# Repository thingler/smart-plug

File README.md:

# Thingler Smart Plug

Thingler Smart Plug is a 3D printed smart plug based on the popular ESP32 micro controller. This device is using the [Thingler ESP32-PICO Module](https://github.com/thingler/esp32-pico-module).

Software has been written to either connect to the [AWS IOT service](https://github.com/thingler/smart-plug-esp32) or it can use the [Matter connectrivity standard](https://github.com/thingler/smart-plug-matter).

## Getting started

### Requirements

* [KiCad](https://www.kicad.org/download/) for the schematics
* [Thingler ESP32-PICO Module](https://github.com/thingler/esp32-pico-module)
* Either [Thingler Smart Plug Matter](https://github.com/thingler/smart-plug-matter) or [Thinger Smart Plug ESP32 (AWS IoT)](https://github.com/thingler/smart-plug-esp32) for the ESP32 module
* [3D design](https://www.tinkercad.com/things/a5thrdSu9my)

### Build

#### Disclamer

Thingler Smart Plug is provided for informational and educational purposes only. The creator of the project and its contributors are not responsible for any damages, injuries, or losses that may result from building, modifying, or using the smart plug. Users assume all risks associated with building and using the smart plug, and should take all necessary precautions to ensure their safety. By using the smart plug or any information provided in this project, users agree to hold harmless the creator and contributors of the project from any and all claims, damages, or expenses that may arise.

> :warning: **Warning: The Smart Plug is designed to work with high voltage AC power from the electrical outlet. This voltage can be dangerous and even deadly if not handled properly. Only experienced individuals with proper training and knowledge should attempt to build this smart plug. If you are not experienced or confident in your ability to work with high voltage electricity, do not attempt to build or use this device. Improper use or handling of the smart plug can result in serious injury or death. Always take appropriate safety measures and precautions when working with high voltage electricity.**

> :warning: **Warning: The circuit does not provide galvanic isolation, which means that dangerous voltages from the AC power line can be present in the circuit. Do not attempt to connect any instruments or devices to the circuit while it is connected to the AC power line.**

#### Components

The PCB can be ordered from any fabrication houses by providing the [gerber files](Gerbers). Note that the copper weight should be 2 oz.

The following components has been used for Smart Plug:

| Ref | Qty | Manufacturer Part Number | Manufacturer | Description | Product Link |
| --- | --- | --- | --- | --- | --- |
| C1, C2, C3, C5, C6 | 5 | C1206C104M5RACTU | KEMET | Multilayer Ceramic Capacitors MLCC - SMD/SMT 50V 0.1uF X7R 1206 20% | [Mouser](https://www.mouser.com/ProductDetail/KEMET/C1206C104M5RACTU?qs=sGAEpiMZZMs0AnBnWHyRQAyQ3AEn5kTUXS61cVd4nXQ%3D) |
| C4 | 1 | TPSE477K010R0050 | KYOCERA AVX | Tantalum Capacitors - Solid SMD 10V 470uF 10% 2917 ESR= 50 mOhm | [Mouser](https://www.mouser.com/ProductDetail/KYOCERA-AVX/TPSE477K010R0050?qs=sGAEpiMZZMsh%252B1woXyUXjxWZTFtyFwDuJgYiJSpALQg%3D) |
| C7 | 1 | C3216X7S0J336M160AC | TDK | Multilayer Ceramic Capacitors MLCC - SMD/SMT 1206 6.3V 33uF X7S 20% T: 1.6mm | [Mouser](https://www.mouser.com/ProductDetail/TDK/C3216X7S0J336M160AC?qs=xLDY6iXSiQZFXqsBpUFNJw%3D%3D) |
| D1 | 1 | ABS10A-13 | Diodes Incorporated | Bridge Rectifier | [Mouser](https://www.mouser.com/ProductDetail/Diodes-Incorporated/ABS10A-13?qs=5aG0NVq1C4z7Y6XEf8aBrg%3D%3D) |
| F1 | 1 | 0679H1000-01 | Bel Fuse | Surface Mount Fuse 1A 350 VAC 72 VCD | [Mouser](https://www.mouser.com/ProductDetail/530-0679H1000-01) |
| J1-1 | 1 |  | ZHNL | Europe Standard Plug Insert, can only be acquired in big quantities (or as samples) | [Alibaba](https://www.alibaba.com/product-detail/Europe-Standard-Plug-Insert-two-2_1600487104594.html) |
| J1-2 | 1 |  | ZHNL | AMD European German socket, can only be acquired in big quantities (or as samples) | [Zhnlen](http://www.zhnlen.com/en/pd.jsp?recommendFromPid=0&id=221&fromMid=827&fromColId=116), [Alibaba](https://www.alibaba.com/product-detail/German-and-serbia-Terminal-Contact-Cage_1600497363416.html) |
| L1 | 1 | ME3220-123KLC | Coilcraft | Power Inductors - SMD 12uH Unshld 10% 840mA 470mOhms | [Mouser](https://www.mouser.com/ProductDetail/Coilcraft/ME3220-123KLC?qs=sGAEpiMZZMsg%252By3WlYCkU2kWFds1hA9DbYDsvlhd31E%3D) |
| Q1 | 1 | STGD5NB120SZT4 | STMicroelectronics | IGBT Transistors N-Ch 1200 Volt 5 Amp | [Mouser](https://www.mouser.com/ProductDetail/STMicroelectronics/STGD5NB120SZT4?qs=Tj7OqeScv5KzkQtpY0oojQ%3D%3D) |
| Q2 | 1 | BTA316B-600E,118 | WeEn Semiconductors | Triacs Thyristor TRIAC 600V 150A 3-Pin (2+Tab) | [Mouser](https://www.mouser.com/ProductDetail/WeEn-Semiconductors/BTA316B-600E118?qs=6YAT8rHPFU%252BjXw0I0rTt4g%3D%3D) |
| R1, R2 | 2 | CR1206AFX-2003EAS | Bourns | Thick Film Resistors - SMD ResA-AS 1206 200k 1% 250mW TC100 | [Mouser](https://www.mouser.com/ProductDetail/Bourns/CR1206AFX-2003EAS?qs=PzGy0jfpSMsbNqkCSMTFTg%3D%3D) |
| R3, R4 | 2 | KTR18EZPF5103 | ROHM Semiconductor | Thick Film Resistors - SMD 1206 510Kohm 1% High VoltageAEC-Q200 | [Mouser](https://www.mouser.com/ProductDetail/ROHM-Semiconductor/KTR18EZPF5103?qs=DyUWGjl%252BcVuYEq26lvIerQ%3D%3D) |
| R5 | 1 | CRCW1206210RFKEA | Vishay / Dale | Thick Film Resistors - SMD 1/4watt 210ohms 1% | [Mouser](https://www.mouser.com/ProductDetail/Vishay-Dale/CRCW1206210RFKEA?qs=LOE%2FbrHKynXo3sZGow1Zgw%3D%3D) |
| R6 | 1 | CRCW120680K6FKEA | Vishay / Dale | Thick Film Resistors - SMD 1/4watt 80.6Kohms 1% | [Mouser](https://www.mouser.com/ProductDetail/Vishay-Dale/CRCW120680K6FKEA?qs=sGAEpiMZZMtlubZbdhIBIIDv3ViF%2FKZ8GQ5VYt9J%2FQI%3D) |
| R7 | 1 | CR1206-FX-1242ELF | Bourns | Thick Film Resistors - SMD 12.4K 1% | [Mouser](https://www.mouser.com/ProductDetail/Bourns/CR1206-FX-1242ELF?qs=sGAEpiMZZMtlubZbdhIBICIt3wBox2Qh6Yrjo1PMsNo%3D) |
| R8 | 1 | ERJ-8ENF1800V | Panasonic | Thick Film Resistors 1206 180ohms 1% AEC-Q200 | [Mouser](https://www.mouser.com/ProductDetail/Panasonic/ERJ-8ENF1800V?qs=sGAEpiMZZMvdGkrng054t8AJgcdMkx7xp%2FUyp6%252BxK6s%3D) |
| U1 | 1 | THINGLER-ESP32-PICO | Thingler | ESP32 module | [GitHub](https://github.com/thingler/esp32-pico-module) |
| U2 | 1 | SR086SG-G | Microchip Technology / Atmel | Switching Voltage Regulators 3.3V Adjust Off-Line Switching Regulator | [Mouser](https://www.mouser.com/ProductDetail/Microchip-Technology-Atmel/SR086SG-G?qs=ph4zPCVRuvrOCUnBv7TdAA%3D%3D) |
| U3 | 1 | FODM3012R2V-NF098 | onsemi / Fairchild | Triac & SCR Output Optocouplers MFP, 250V Random Phase Triac Output | [Mouser](https://www.mouser.com/ProductDetail/onsemi-Fairchild/FODM3012R2V-NF098?qs=0lQeLiL1qyYTpyszibB5tA%3D%3D) |
| U4 | 1 | TPS560430X3FDBVR | Texas Instruments | Voltage Regulators - Switching Regulators SIMPLE SWITCHER 36-V, 600-mA Buck Regulator With High-Efficiency Sleep Mode 6-SOT-23 -40 to 125 | [Mouser](https://www.mouser.com/ProductDetail/Texas-Instruments/TPS560430X3FDBVR?qs=sGAEpiMZZMsMIqGZiACxIY79W%2FZ1FL4F65GEfpgrgpedxebpzRnU7w%3D%3D) |

#### Printing the 3D design

The smart plug case is designed to be printed without the need for any support material. We recommend using PETG filament as it is a strong and durable material suitable for this application. Please note that in addition to the printed case, you will also need the following components to assemble the smart plug:

* 2 x M2 nuts
* 2 x M2 * 8 screws

## License

Released under [GNU/GPL Version 3](LICENSE)

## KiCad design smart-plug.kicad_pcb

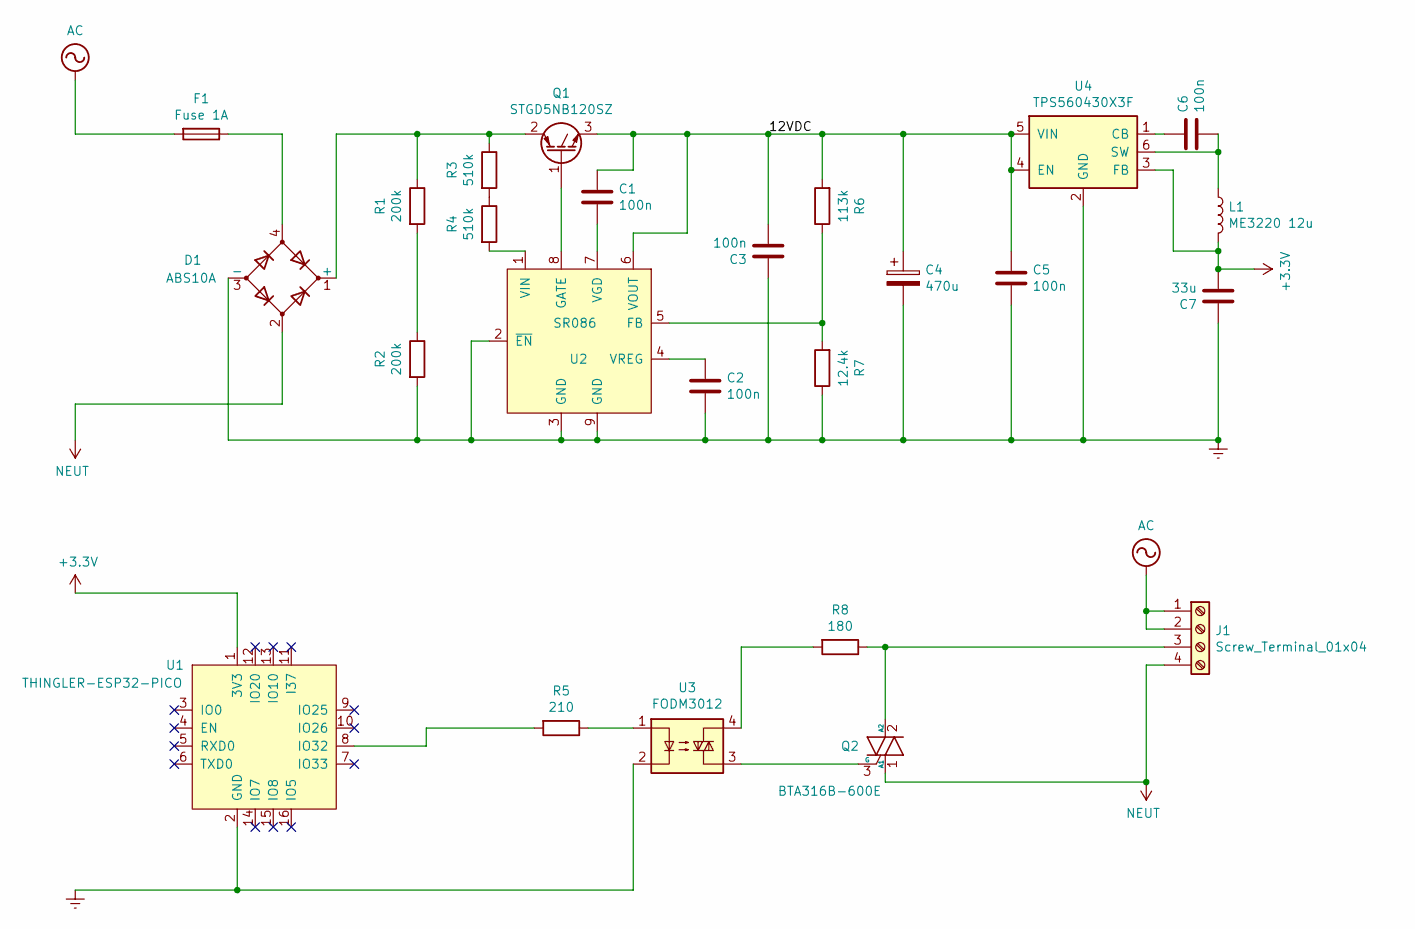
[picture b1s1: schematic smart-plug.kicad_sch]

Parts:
C1, C2, C3, C5, C6: 100n; C_1206_3216Metric_Pad1.42x1.75mm_HandSolder
C4: 470u; CP_EIA-7343-15_Kemet-W
C7: 33u; C_1206_3216Metric_Pad1.42x1.75mm_HandSolder
D1: ABS10A
F1: Fuse 1A; fuse-2410
J1: Screw_Terminal_01x04; 3d_power_connector
L1: ME3220 12u; ME3220
Q1: STGD5NB120SZ; TO-252-2
Q2: BTA316B-600E; to-263-2
R1, R2: 200k; R_1206_3216Metric_Pad1.42x1.75mm_HandSolder
R3, R4: 510k; R_1206_3216Metric_Pad1.42x1.75mm_HandSolder
R5: 210; R_1206_3216Metric_Pad1.42x1.75mm_HandSolder
R6: 113k; R_1206_3216Metric_Pad1.42x1.75mm_HandSolder
R7: 12.4k; R_1206_3216Metric_Pad1.42x1.75mm_HandSolder
R8: 180; R_1206_3216Metric_Pad1.42x1.75mm_HandSolder
U1: THINGLER-ESP32-PICO; Thingler-esp32-vertical
U2: SR086; SOIC-8-1EP_3.9x4.9mm_P1.27mm_EP2.29x3mm
U3: FODM3012
U4: TPS560430X3F; SOT-23-6

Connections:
+3V3: C7.2, L1.2, U1.1 (3V3), U4.3 (FB)
/12VDC: C1.1, C3.2, C4.1, C5.1, Q1.3 (E), R6.2, U2.6 (VOUT), U4.4 (EN), U4.5 (VIN)
AC: F1.2, J1.1, J1.2
Earth: C2.2, C3.1, C4.2, C5.2, C7.1, D1.3 (-), R2.2, R7.1, U1.2 (GND), U2.2 (~EN), U2.3 (GND), U2.9 (GND), U3.2, U4.2 (GND)
NEUT: D1.2, J1.4, Q2.1 (A1)
unnamed: C1.2, U2.7 (VGD)
unnamed: C2.1, U2.4 (VREG)
unnamed: C6.1, U4.1 (CB)
unnamed: C6.2, L1.1, U4.6 (SW)
unnamed: D1.1 (+), Q1.2 (C), R1.1, R3.1
unnamed: D1.4, F1.1
unnamed: J1.3, Q2.2 (A2), R8.1
unnamed: Q1.1 (G), U2.8 (GATE)
unnamed: Q2.3 (G), U3.3
unnamed: R1.2, R2.1
unnamed: R3.2, R4.1
unnamed: R4.2, U2.1 (VIN)
unnamed: R5.1, U3.1
unnamed: R5.2, U1.8 (IO32)
unnamed: R6.1, R7.2, U2.5 (FB)
unnamed: R8.2, U3.4

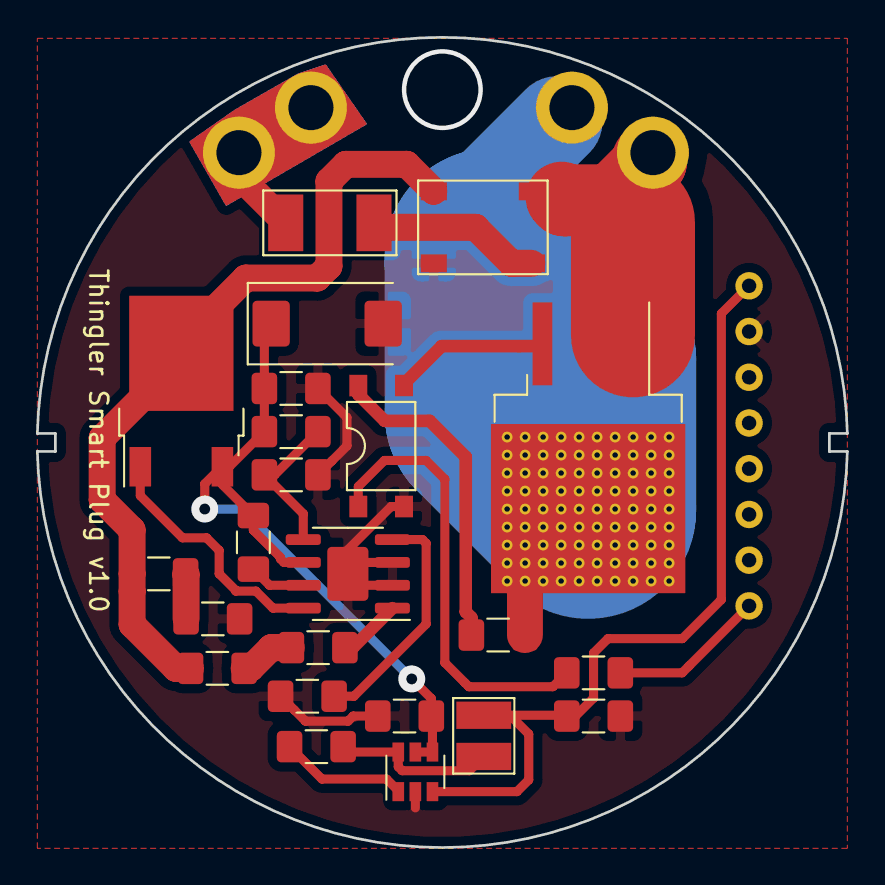
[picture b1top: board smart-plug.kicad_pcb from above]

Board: 2 copper layers, 45.0 x 45.0 mm, 25 parts (1 on the bottom side), 21 nets.

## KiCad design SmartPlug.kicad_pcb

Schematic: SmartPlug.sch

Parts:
C1: X2 150n; C_Axial_L12.0mm_D6.5mm_P15.00mm_Horizontal
C2: 47u; CP_Elec_10x10
C3, C4: 100n; C_1206_3216Metric_Pad1.42x1.75mm_HandSolder
C5: 33u; C_1206_3216Metric_Pad1.42x1.75mm_HandSolder
D1: D_Bridge; Diode_Bridge_Vishay_DFS
D2: 68V Zener; D_SMA_Handsoldering
D3: D_Schottky; D_SOD-123
J1: Conn_WallSocket; 230V_OUT
L1: 200u; L_Coilcraft_LPS4018
Q1: BTA 12/600SW; TO-220-3_Vertical
R1, R2: 383k; R_1206_3216Metric_Pad1.42x1.75mm_HandSolder
R3, R4: 100 1W; R_Axial_DIN0414_L11.9mm_D4.5mm_P15.24mm_Horizontal
R5: 100; R_1206_3216Metric_Pad1.42x1.75mm_HandSolder
R6: 180; R_1206_3216Metric_Pad1.42x1.75mm_HandSolder
R7: 1M; R_1206_3216Metric_Pad1.42x1.75mm_HandSolder
R8: 100k; R_1206_3216Metric_Pad1.42x1.75mm_HandSolder
U1: MAX5033AUSA; SOIC-8_3.9x4.9mm_P1.27mm
U2: ESP32-PICO-KIT
U3: MOC3021M; DIP-6_W8.89mm_SMDSocket_LongPads

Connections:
+3V3: C5.1, L1.2, U1.4, U2.20, U2.38
/+68V: C2.1, D2.1, R3.1, R7.2, U1.7
AC: C1.2, J1.1, R1.2
Earth: C2.2, C3.2, C5.2, D1.2, D2.2, D3.2, R8.1, U1.3, U1.6, U2.19, U2.39, U3.2
NEUT: Q1.1 (A1), R4.2
unnamed: C1.1, D1.3, R2.1
unnamed: C3.1, U1.2
unnamed: C4.1, U1.1
unnamed: C4.2, D3.1, L1.1, U1.8
unnamed: D1.1, R3.2
unnamed: D1.4, R4.1
unnamed: J1.2, Q1.2 (A2), R6.1
unnamed: Q1.3 (G), U3.4
unnamed: R1.1, R2.2
unnamed: R5.1, U3.1
unnamed: R5.2, U2.29
unnamed: R6.2, U3.6
unnamed: R7.1, R8.2, U1.5

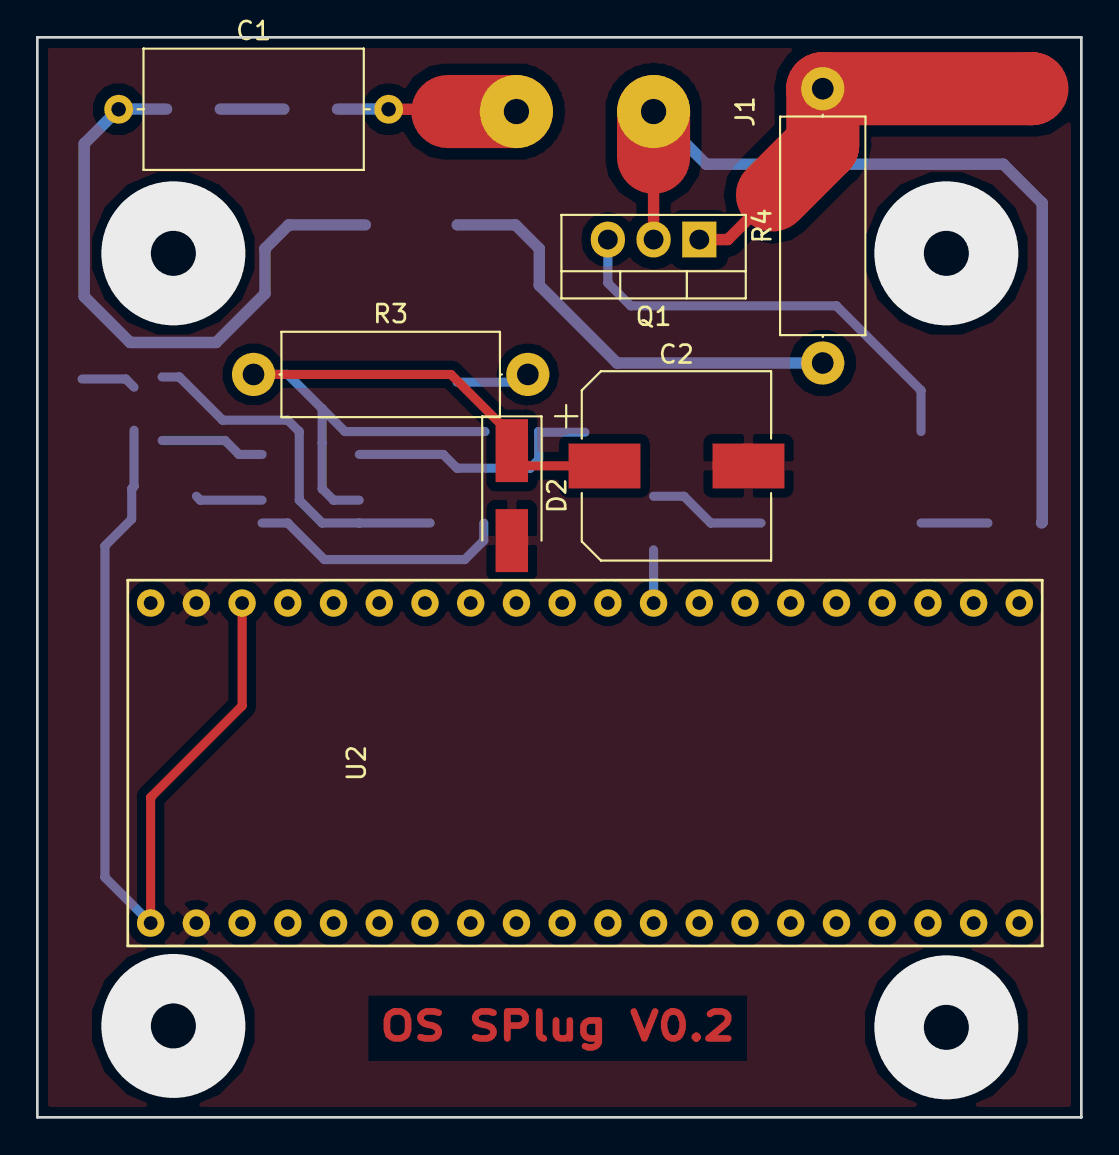
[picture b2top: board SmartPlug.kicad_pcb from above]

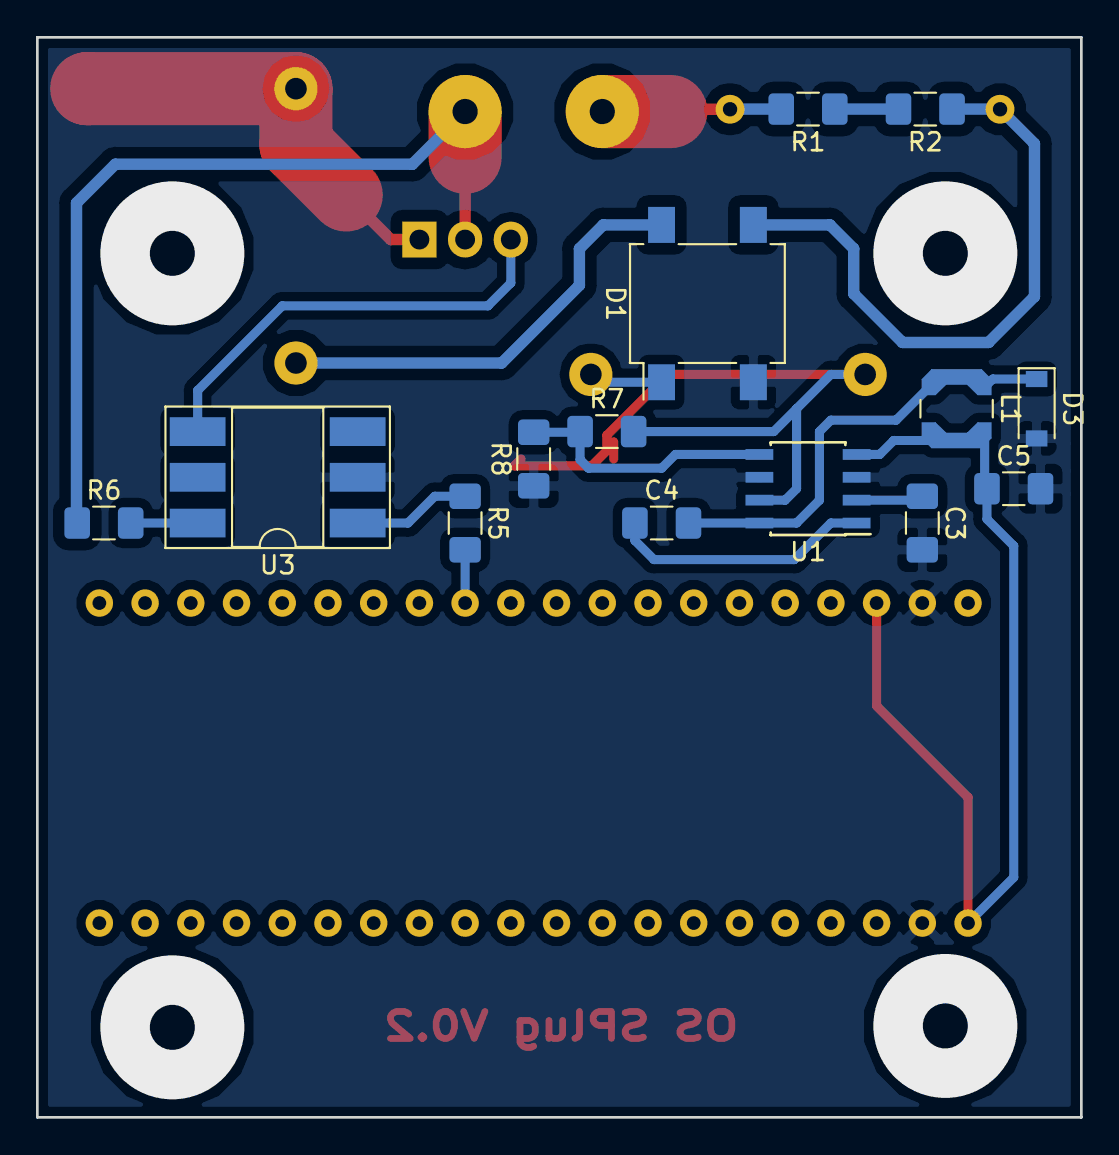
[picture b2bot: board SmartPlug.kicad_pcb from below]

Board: 2 copper layers, 58.0 x 60.0 mm, 22 parts (14 on the bottom side), 18 nets.

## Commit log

2019-02-06 adding schematics
2020-01-19 version 0.5
2020-01-19 removed rescue library
2020-07-29 rename project
2020-07-30 Schematics for voltage and current measurements
2020-08-02 pcb for voltage and current measurements
2021-06-03 Thingler 3D Smart Plug
2021-06-10 small design improvements
2021-06-10 Thingler Smart Plug schematics for 3D print (#1)
2021-06-10 increased width for power traces
2023-02-15 Introduction to the docs
2023-02-15 License and more docs
2023-02-16 Component list
2023-02-16 Improved discalmer and few words about printing
